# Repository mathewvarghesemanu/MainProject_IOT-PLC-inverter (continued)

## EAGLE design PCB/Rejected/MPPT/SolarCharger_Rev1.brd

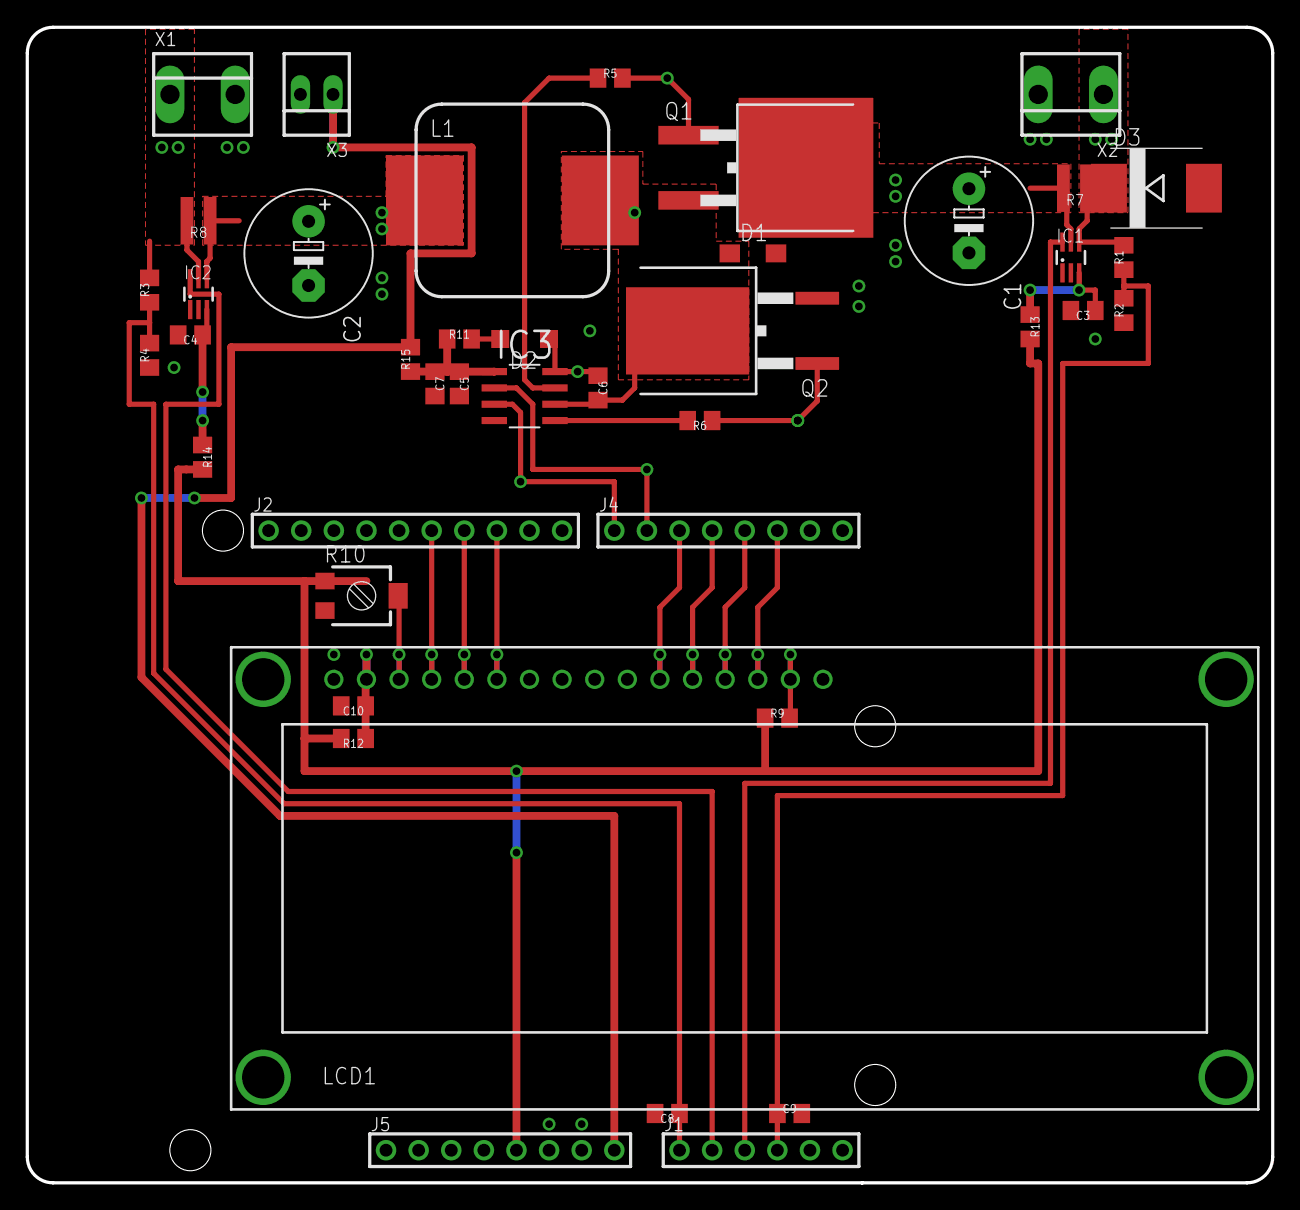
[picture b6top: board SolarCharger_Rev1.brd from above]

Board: 2 copper layers, 97.0 x 90.0 mm, 42 parts (0 on the bottom side), 33 nets.

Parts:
C1: 680u; 10MM
C2: 820u; 10MM
C3, C4, C5, C6, C8, C9, C10: 100n; C0805
C7: 1u; C0805
D1: SCHOTTKYMINI2; MINI2-F3-B
D2: SCHOTTKYSOD123; SOD123
D3: 20V; SMC
IC1, IC2: INA213LONG; SC70-6_LONG
IC3: IR2104; SOIC8
J1: Analog; 100MIL_6X_ROUND
J2: Digital2; 100MIL_10X_ROUND
J4: Digital1; 100MIL_8X_ROUND
J5: Power; 100MIL_8X_ROUND
L1: 100u; MSS1583
LCD1: LCD_2X16
Q1: IPB136N08N3; TO263-3
Q2: IPB136N08N3; TO263-3@1
R1: 39k; R0805
R2, R4: 10k; R0805
R3: 22k; R0805
R5, R6, R11: 10; R0805
R7: R022; 0612
R8: R016; 0612
R9: 220; R0805
R10: 10k; RTRIM3314G
R12, R13, R14, R15: 0R; R0805
X1: Battery; 200MIL_2X
X2: Pannel; 200MIL_2X
X3: Supply; 22-23-2021

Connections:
!SD!: IC3.3, J4.1
+5V: J5.5, R9.1, R10.CW, R12.2, R13.2, R14.2
+12V: J5.8, R15.2, X3.1
BATTERY: IC2.5, R3.2, R8.2, X1.1
D4: J4.3, LCD1.11
D5: J4.4, LCD1.12
D6: J4.5, LCD1.13
D7: J4.6, LCD1.14
E: J2.8, LCD1.6
GND: C1.-, C2.-, C3.2, C4.2, C5.2, C7.2, C8.2, C9.2, C10.2, D1.A, D3.A, IC1.1, IC1.2, IC2.1, IC2.2, IC3.4, J5.6, J5.7, LCD1.1, LCD1.16, LCD1.DRILL@1, LCD1.DRILL@2, LCD1.DRILL@3, LCD1.DRILL@4, Q2.3, R2.1, R4.1, R10.CCW, X1.2, X2.2, X3.2
IIN_SENSE: IC1.6, J1.3
IOUT_SENSE: IC2.6, J1.2
unnamed: C10.1, LCD1.2, R12.1
unnamed: C3.1, IC1.3, R13.1
unnamed: C4.1, IC2.3, R14.1
unnamed: Q1.1, R5.2
unnamed: C5.1, C7.1, IC3.1, R11.1, R15.1
unnamed: Q2.1, R6.1
unnamed: LCD1.15, R9.2
unnamed: LCD1.3, R10.WIPER
unnamed: D2.A, R11.2
unnamed: C6.1, D2.C, IC3.8
unnamed: IC3.7, R5.1
unnamed: IC3.5, R6.2
PANNEL: D3.C, IC1.4, R1.2, R7.1, X2.1
PWM: IC3.2, J4.2
RS: J2.6, LCD1.4
RW: J2.7, LCD1.5
SWITCHNODE: C6.2, D1.C, IC3.6, L1.2, Q1.3, Q2.TAB
VIN: C1.+, IC1.5, Q1.TAB, R7.2
VIN_SENSE: C9.1, J1.4, R1.1, R2.2
VOUT: C2.+, IC2.4, L1.1, R8.1
VOUT_SENSE: C8.1, J1.1, R3.1, R4.2

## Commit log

2019-04-14 PCB added
    Incomplete PCB
2020-01-17 final
